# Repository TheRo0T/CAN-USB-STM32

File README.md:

# CAN-USB-STM32
CAN-USB adapter based on [STM32F105](http://www.st.com/web/en/catalog/mmc/SC1169/SS1031/LN1564) microprocessor

Fault tolerant [CAN](https://en.wikipedia.org/wiki/CAN) using [TJA1055T](http://www.nxp.com/products/interface_and_connectivity/can_lin_flexray_transceivers/can_transceivers/TJA1055T.html)

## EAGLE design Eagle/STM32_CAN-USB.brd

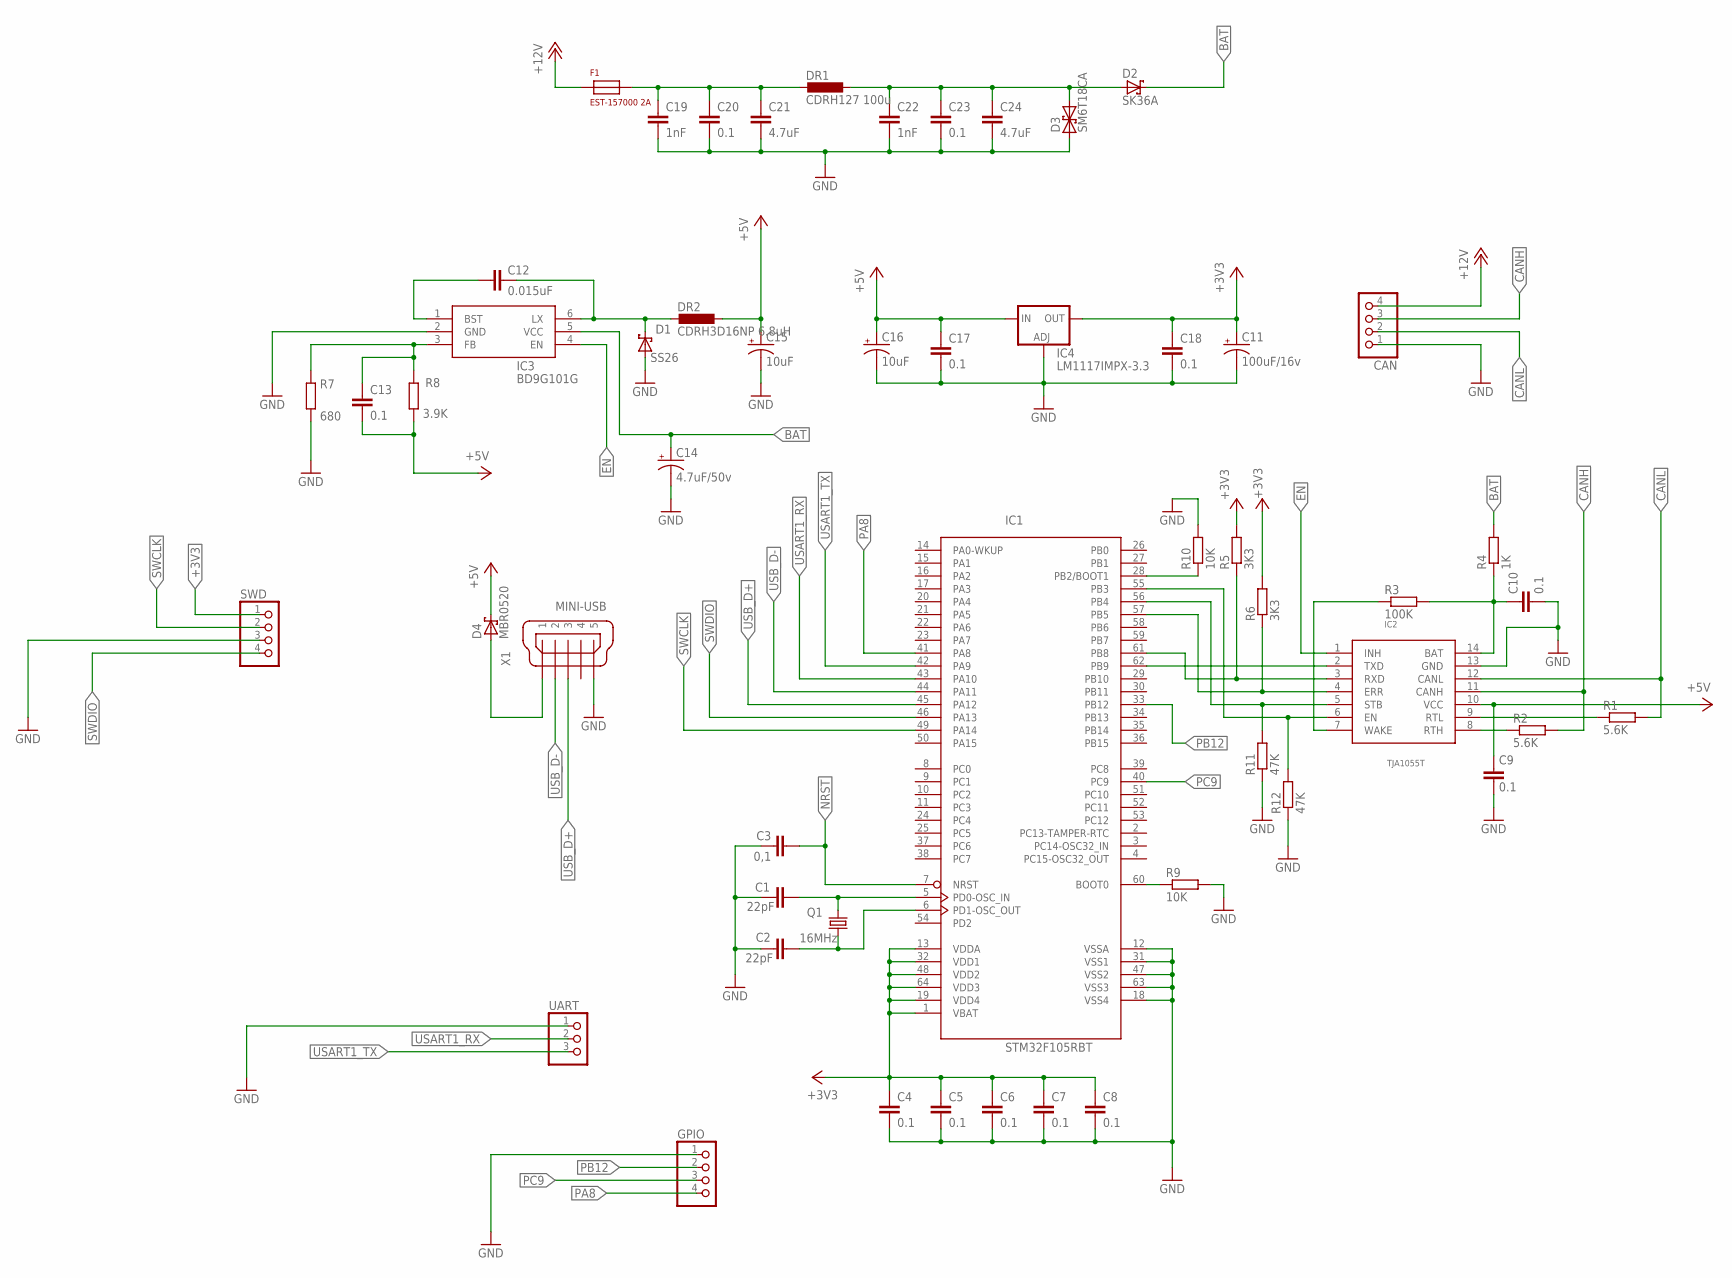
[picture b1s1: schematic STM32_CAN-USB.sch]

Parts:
C1, C2: 22pF; C0805
C3: 0,1; C0805
C4, C5, C6, C7, C8, C9, C10, C13, C17, C18, C20, C23: 0.1; C0805
C11: 100uF/16v; 153CLV-0605
C12: 0.015uF; C0805
C14: 4.7uF/50v; 153CLV-0605
C15, C16: 10uF; 153CLV-0605
C19, C22: 1nF; C0805
C21, C24: 4.7uF; C0805
CAN: PINHD-1X4; 1X04
D1: SS26; SMB
D2: SK36A; DO-214AC
D3: SM6T18CA; DO214AA
D4: MBR0520; SOD123
DR1: CDRH127 100u; MS85
DR2: CDRH3D16NP 6.8uH; CDRH3D16NP
F1: EST-157000 2A; FUSE
GPIO: PINHD-1X4; 1X04
IC1: STM32F105RBT; LQFP64
IC2: TJA1055T; SO-14W
IC3: BD9G101G; SSOP6
IC4: LM1117IMPX-3.3; SOT223
Q1: 16MHz; HC49UP
R1, R2: 5.6K; R0805
R3: 100K; R0805
R4: 1K; R0805
R5, R6: 3K3; R0805
R7: 680; R0805
R8: 3.9K; R0805
R9, R10: 10K; R0805
R11, R12: 47K; R0805
SWD: PINHD-1X4; 1X04
UART: PINHD-1X3; 1X03
X1: MINI-USB; UX60-MB-5ST

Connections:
+3V3: C4.1, C5.1, C6.1, C7.1, C8.1, C11.+, C18.1, IC1.1 (VBAT), IC1.13 (VDDA), IC1.19 (VDD4), IC1.32 (VDD1), IC1.48 (VDD2), IC1.64 (VDD3), IC4.2 (OUT), IC4.4 (OUT), R5.2, R6.2, SWD.1
+5V: C9.1, C13.2, C15.+, C16.+, C17.1, D4.C, DR2.P$2 (2), IC2.10 (VCC), IC4.3 (IN), R8.1
+12V: CAN.4, F1.P$1 (1)
BAT: C14.+, D2.C, IC3.5 (VCC), R4.2
CANH: CAN.3, IC2.11 (CANH), R2.2
CANL: CAN.2, IC2.12 (CANL), R1.2
EN: IC2.1 (INH), IC3.4 (EN)
GND: C1.2, C2.2, C3.1, C4.2, C5.2, C6.2, C7.2, C8.2, C9.2, C10.2, C11.-, C14.-, C15.-, C16.-, C17.2, C18.2, C19.2, C20.2, C21.2, C22.2, C23.2, C24.2, CAN.1, D1.A, D3.A (1), GPIO.1, IC1.12 (VSSA), IC1.18 (VSS4), IC1.31 (VSS1), IC1.47 (VSS2), IC1.63 (VSS3), IC2.13 (GND), IC3.2 (GND), IC4.1 (ADJ), R7.1, R9.2, R10.2, R11.1, R12.1, SWD.3, UART.1, X1.5, X1.M1 (5), X1.M2 (5)
unnamed: C1.1, IC1.5 (PD0-OSC_IN), Q1.2
unnamed: C2.1, IC1.6 (PD1-OSC_OUT), Q1.1
unnamed: IC1.60 (BOOT0), R9.1
unnamed: IC1.61 (PB8), IC2.3 (RXD), R5.1
unnamed: IC1.62 (PB9), IC2.2 (TXD)
unnamed: IC1.56 (PB4), IC2.5 (STB), R11.2
unnamed: IC2.8 (RTH), R2.1
unnamed: IC2.9 (RTL), R1.1
unnamed: C12.1, IC3.1 (BST)
unnamed: IC2.7 (WAKE), R3.1
unnamed: C10.1, IC2.14 (BAT), R3.2, R4.1
unnamed: C12.2, D1.C, DR2.P$1 (1), IC3.6 (LX)
unnamed: C13.1, IC3.3 (FB), R7.2, R8.2
unnamed: IC1.55 (PB3), IC2.6 (EN), R12.2
unnamed: IC1.57 (PB5), IC2.4 (ERR), R6.1
unnamed: IC1.28 (PB2/BOOT1), R10.1
unnamed: C22.1, C23.1, C24.1, D2.A, D3.C (2), DR1.P$2 (2)
unnamed: C19.1, C20.1, C21.1, DR1.P$1 (1), F1.P$2 (2)
unnamed: D4.A, X1.1
NRST: C3.2, IC1.7 (NRST)
PA8: GPIO.4, IC1.41 (PA8)
PB12: GPIO.2, IC1.33 (PB12)
PC9: GPIO.3, IC1.40 (PC9)
SWCLK: IC1.49 (PA14), SWD.2
SWDIO: IC1.46 (PA13), SWD.4
USART1_RX: IC1.43 (PA10), UART.2
USART1_TX: IC1.42 (PA9), UART.3
USB_D+: IC1.45 (PA12), X1.3
USB_D-: IC1.44 (PA11), X1.2

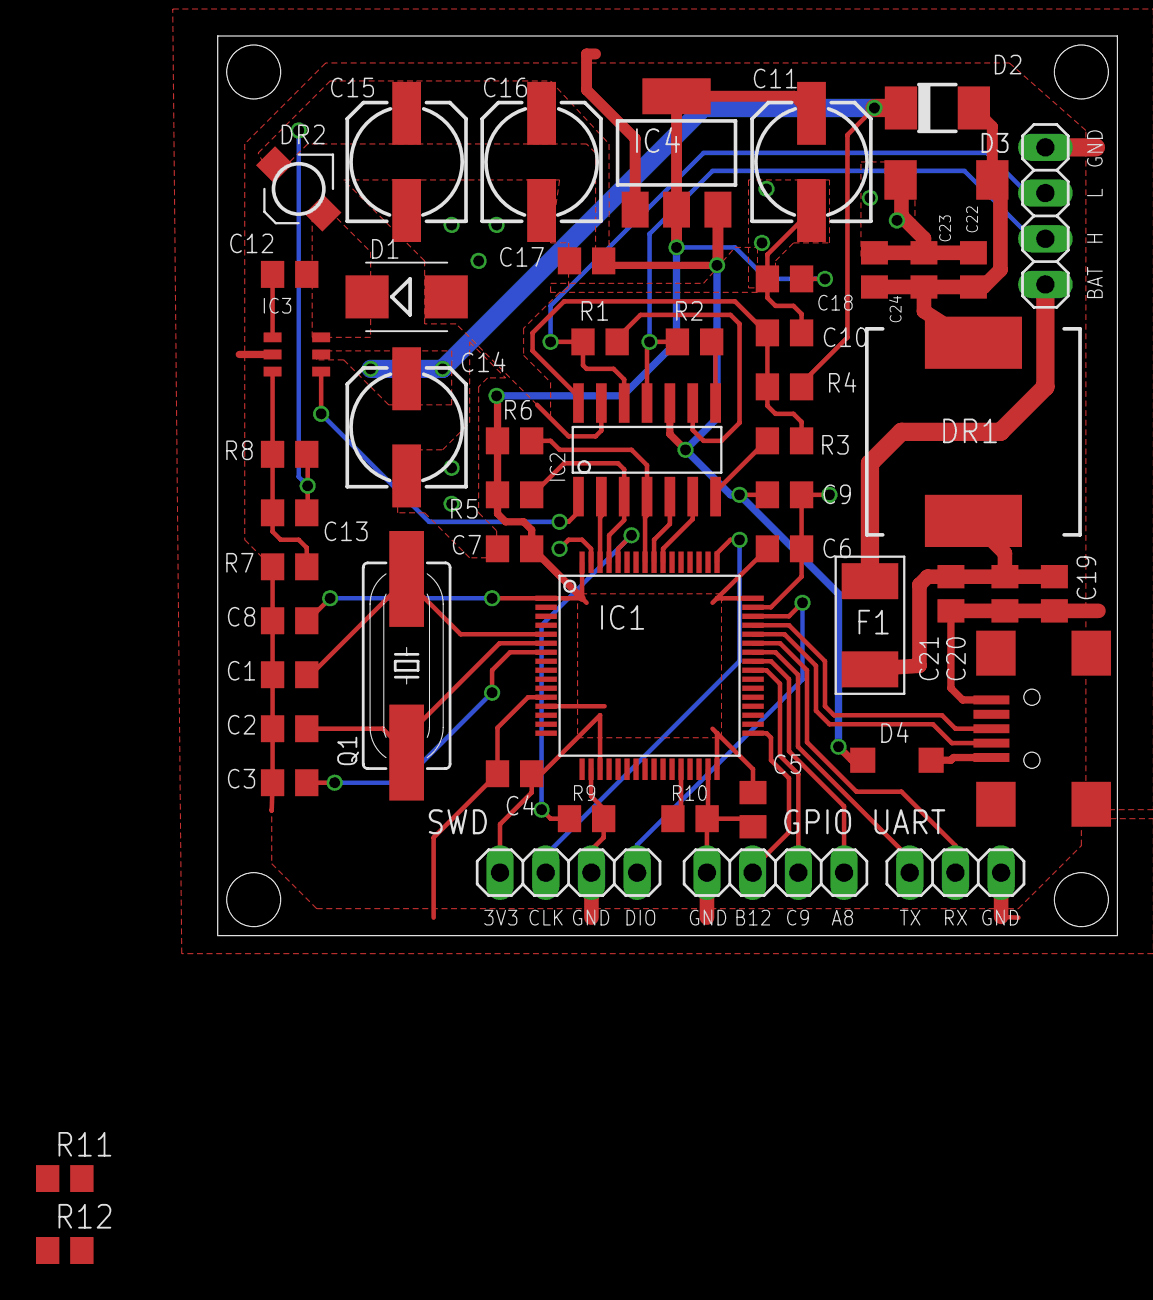
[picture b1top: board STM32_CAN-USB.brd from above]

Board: 2 copper layers, 50.0 x 50.0 mm, 53 parts (0 on the bottom side), 37 nets.

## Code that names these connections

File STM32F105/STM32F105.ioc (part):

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Mcu.Name=STM32F105R(8-B-C)Tx
Mcu.Package=LQFP64
Mcu.UserName=STM32F105RBTx
PA10.Mode=Asynchronous
PA10.Signal=USART1_RX
PA11.Mode=Device_Only
PA11.Signal=USB_OTG_FS_DM
PA12.Mode=Device_Only
PA12.Signal=USB_OTG_FS_DP
PA13.Mode=Serial_Wire
PA13.Signal=SYS_JTMS-SWDIO
PA14.Mode=Serial_Wire
PA14.Signal=SYS_JTCK-SWCLK
PA9.Mode=Asynchronous
PA9.Signal=USART1_TX
PB5.GPIOParameters=GPIO_Label
PB5.GPIO_Label=TJA_EN
PB5.Signal=GPIO_Output
PB6.GPIOParameters=GPIO_Label
PB6.GPIO_Label=TJA_STB
PB6.Signal=GPIO_Output
PB7.GPIOParameters=GPIO_Label
PB7.GPIO_Label=TJA_ERR
PB7.Signal=GPIO_Input
PB8.Mode=Master
PB8.Signal=CAN1_RX
PB9.Mode=Master
PB9.Signal=CAN1_TX
PD0-OSC_IN.Mode=HSE-External-Oscillator
PD0-OSC_IN.Signal=RCC_OSC_IN
PD1-OSC_OUT.Mode=HSE-External-Oscillator
PD1-OSC_OUT.Signal=RCC_OSC_OUT
RCC.HSEDivPLL=RCC_HSE_PREDIV_DIV2
RCC.HSE_VALUE=16000000
RCC.SYSCLKFreq_VALUE=72000000
RCC.SYSCLKSource=RCC_SYSCLKSOURCE_PLLCLK
board=STM32F105

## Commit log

2015-09-22 First Sheme
2015-09-22 backup
2015-09-22 Revert "backup"
    This reverts commit 257f3c0ff6883532fde8ce6fbba55451b8b6f85a.
    # Conflicts:
    # README.md
2015-09-22 test
2015-09-22 test2
2015-11-04 SWD pin labels
2015-11-05 change scheme, unrouted board
2015-11-05 TJA networks names
2015-11-05 Move eagle files to subfolder
2015-11-05 Add eclipse project
2015-11-05 Enable USB CDC
2015-11-05 USART TX DMA
2015-11-08 UART RX via DMA
2015-11-08 Remove rxUart declaration, remove type cast warnings
2015-11-09 Extract utils file
2015-11-09 Refactor canhacker code
2015-11-09 Transmit & Receive 11bit RTR
2015-11-10 Timestamps
2015-11-11 Revert sch & brd
2015-11-11 CAN pin labels
2015-11-11 TJA1055 library prototype
2015-11-12 Labels, pin headers optimization
2015-11-16 added pull-down resistors on the lines EN and STB
2015-11-19 TJA: Proper GPIO initialization
2015-11-19 Remove CAN RX1
2015-11-19 Fix HAL CAN Rcv/Trmt issue
2015-11-19 General improvements
